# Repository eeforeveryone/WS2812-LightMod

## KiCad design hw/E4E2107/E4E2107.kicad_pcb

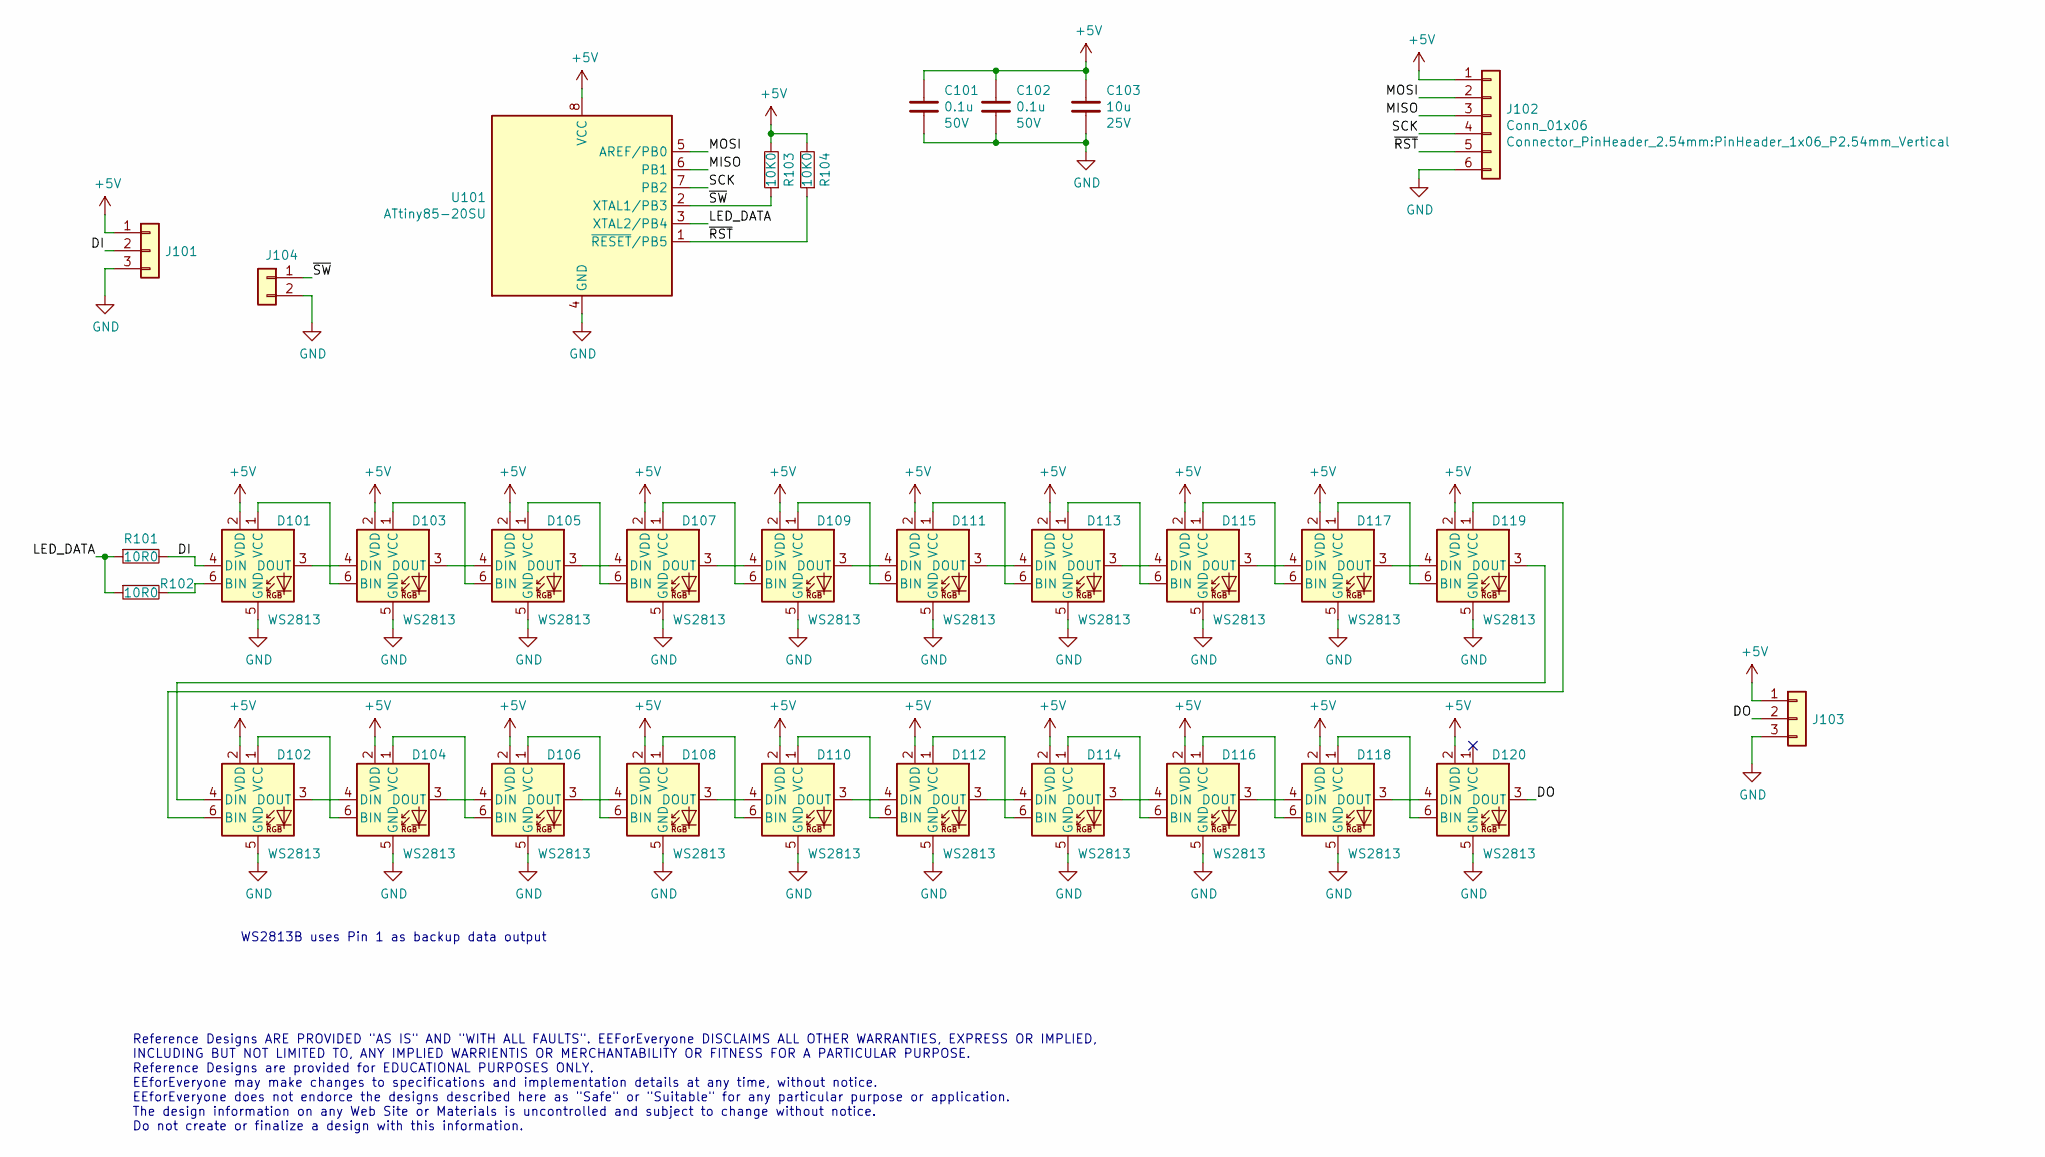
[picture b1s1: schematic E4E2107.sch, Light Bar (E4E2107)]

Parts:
C101, C102: Samsung_0603_0.1u_50V_X7R; C_0603_1608Metric; Voltage 50V; MFG_PN CL10B104KB8NNNC; LCSC C14663
C103: Samsung_0805_10u_25V_X5R; C_0805_2012Metric; Voltage 25V; MFG_PN CL21A106KAYNNNE; LCSC C15850
D101, D102, D103, D104, D105, D106, D107, D108, D109, D110, D111, D112, D113, D114, D115, D116, D117, D118, D119, D120: WS2813; LED_WS2812_PLCC6_5.0x5.0mm_P1.6mm
J101, J103: Conn_01x03; PinHeader_1x03_P2.54mm_Vertical
J102: Conn_01x06; PinHeader_1x06_P2.54mm_Vertical
J104: Conn_01x02; PinHeader_1x02_P2.54mm_Vertical
R101, R102: Yageo_0603_10R0_1pct; R_0603_1608Metric; MFG_PN RC0603FR-0710RL; LCSC C22859
R103, R104: Yageo_0603_10K0_1pct; R_0603_1608Metric; MFG_PN RC0603FR-0710KL; LCSC C25804
U101: ATtiny85-20SU; SOIJ-8_5.3x5.3mm_P1.27mm

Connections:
+5V: C101.1, C102.1, C103.1, D101.2 (VDD), D102.2 (VDD), D103.2 (VDD), D104.2 (VDD), D105.2 (VDD), D106.2 (VDD), D107.2 (VDD), D108.2 (VDD), D109.2 (VDD), D110.2 (VDD), D111.2 (VDD), D112.2 (VDD), D113.2 (VDD), D114.2 (VDD), D115.2 (VDD), D116.2 (VDD), D117.2 (VDD), D118.2 (VDD), D119.2 (VDD), D120.2 (VDD), J101.1, J102.1, J103.1, R103.2, R104.2, U101.8 (VCC)
/DI: D101.4 (DIN), J101.2, R101.2
/DO: D120.3 (DOUT), J103.2
/LED_DATA: R101.1, R102.1, U101.3 (XTAL2/PB4)
/MISO: J102.3, U101.6 (PB1)
/MOSI: J102.2, U101.5 (AREF/PB0)
/SCK: J102.4, U101.7 (PB2)
/~RST: J102.5, R104.1, U101.1 (~RESET~/PB5)
/~SW: J104.1, R103.1, U101.2 (XTAL1/PB3)
GND: C101.2, C102.2, C103.2, D101.5 (GND), D102.5 (GND), D103.5 (GND), D104.5 (GND), D105.5 (GND), D106.5 (GND), D107.5 (GND), D108.5 (GND), D109.5 (GND), D110.5 (GND), D111.5 (GND), D112.5 (GND), D113.5 (GND), D114.5 (GND), D115.5 (GND), D116.5 (GND), D117.5 (GND), D118.5 (GND), D119.5 (GND), D120.5 (GND), J101.3, J102.6, J103.3, J104.2, U101.4 (GND)
unnamed: D101.1 (VCC), D103.6 (BIN)
unnamed: D101.3 (DOUT), D103.4 (DIN)
unnamed: D101.6 (BIN), R102.2
unnamed: D102.1 (VCC), D104.6 (BIN)
unnamed: D102.3 (DOUT), D104.4 (DIN)
unnamed: D102.4 (DIN), D119.3 (DOUT)
unnamed: D102.6 (BIN), D119.1 (VCC)
unnamed: D103.1 (VCC), D105.6 (BIN)
unnamed: D103.3 (DOUT), D105.4 (DIN)
unnamed: D104.1 (VCC), D106.6 (BIN)
unnamed: D104.3 (DOUT), D106.4 (DIN)
unnamed: D105.1 (VCC), D107.6 (BIN)
unnamed: D105.3 (DOUT), D107.4 (DIN)
unnamed: D106.1 (VCC), D108.6 (BIN)
unnamed: D106.3 (DOUT), D108.4 (DIN)
unnamed: D107.1 (VCC), D109.6 (BIN)
unnamed: D107.3 (DOUT), D109.4 (DIN)
unnamed: D108.1 (VCC), D110.6 (BIN)
unnamed: D108.3 (DOUT), D110.4 (DIN)
unnamed: D109.1 (VCC), D111.6 (BIN)
unnamed: D109.3 (DOUT), D111.4 (DIN)
unnamed: D110.1 (VCC), D112.6 (BIN)
unnamed: D110.3 (DOUT), D112.4 (DIN)
unnamed: D111.1 (VCC), D113.6 (BIN)
unnamed: D111.3 (DOUT), D113.4 (DIN)
unnamed: D112.1 (VCC), D114.6 (BIN)
unnamed: D112.3 (DOUT), D114.4 (DIN)
unnamed: D113.1 (VCC), D115.6 (BIN)
unnamed: D113.3 (DOUT), D115.4 (DIN)
unnamed: D114.1 (VCC), D116.6 (BIN)
unnamed: D114.3 (DOUT), D116.4 (DIN)
unnamed: D115.1 (VCC), D117.6 (BIN)
unnamed: D115.3 (DOUT), D117.4 (DIN)
unnamed: D116.1 (VCC), D118.6 (BIN)
unnamed: D116.3 (DOUT), D118.4 (DIN)
unnamed: D117.1 (VCC), D119.6 (BIN)
unnamed: D117.3 (DOUT), D119.4 (DIN)
unnamed: D118.1 (VCC), D120.6 (BIN)
unnamed: D118.3 (DOUT), D120.4 (DIN)

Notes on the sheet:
WS2813B uses Pin 1 as backup data output
Reference Designs ARE PROVIDED "AS IS" AND "WITH ALL FAULTS". EEForEveryone DISCLAIMS ALL OTHER WARRANTIES, EXPRESS OR IMPLIED, INCLUDING BUT NOT LIMITED TO, ANY IMPLIED WARRIENTIS OR MERCHANTABILITY OR FITNESS FOR A PARTICULAR PURPOSE. Reference Designs are provided for EDUCATIONAL PURPOSES ONLY. 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

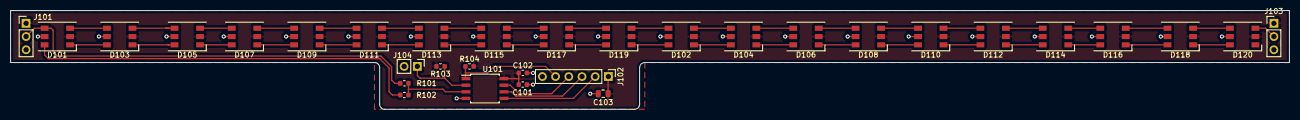
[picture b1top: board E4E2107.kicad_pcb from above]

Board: 2 copper layers, 246.0 x 19.0 mm, 32 parts (0 on the bottom side), 49 nets.

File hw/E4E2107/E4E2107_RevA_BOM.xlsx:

Date: | 44239
Tool: | Eeschema (5.1.6)-1
Component Count: | 32
Item | Qty | Reference(s) | MFG | MFG_PN | Value_Show | Datasheet | Footprint | LCSC
1 | 2 | C101, C102 | Samsung Electro-Mechanics | CL10B104KB8NNNC | 0.1u | https://www.digikey.com/product-detail/en/samsung-electro-me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 | Capacitor_SMD:C_0603_1608Metric | C14663
2 | 1 | C103 | Samsung Electro-Mechanics | CL21A106KAYNNNE | 10u | https://www.digikey.com/product-detail/en/samsung-electro-me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 | Capacitor_SMD:C_0805_2012Metric | C15850
3 | 20 | D101, D102, D103, D104, D105, D106, D107, D108, D109, D110, D111, D112, D113, D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 | Seeed Technology Co., Ltd | 601000200 | WS2813B | https://media.digikey.com/pdf/Data%20Sheets/Seeed%20Technolo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 | LED_SMD:LED_WS2812_PLCC6_5.0x5.0mm_P1.6mm | ~
4 | 2 | J101, J103 |  |  | 1x03 PinHeader |  |  | ~
5 | 1 | J104 |  |  | 1x02 PinHeader | ~ | Connector_PinHeader_2.54mm:PinHeader_1x02_P2.54mm_Vertical | ~
6 | 1 | J102 |  |  | 1x06 PinHeader | ~ | Connector_PinHeader_2.54mm:PinHeader_1x06_P2.54mm_Vertical | ~
7 | 2 | R101, R102 | Yageo | RC0603FR-0710RL | 10R0 | https://www.digikey.com/products/en/resistors/chip-resistor-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 | Resistor_SMD:R_0603_1608Metric | C22859
8 | 2 | R103, R104 | Yageo | RC0603FR-0710KL | 10K0 | https://www.digikey.com/product-detail/en/yageo/RC0603FR-071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 | Resistor_SMD:R_0603_1608Metric | C25804
9 | 1 | U101 | Microchip Technology | ATTINY85-20SU | SO:SOIJ-8 SO:SOIJ-8 | https://www.digikey.com/en/products/detail/microchip-technol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 | Package_SO:SOIJ-8_5.3x5.3mm_P1.27mm | ~

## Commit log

2021-08-28 initial commit
    added repo with HW & SW
